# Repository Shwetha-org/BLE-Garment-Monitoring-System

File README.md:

# BLE Garment Monitoring System

## Overview

This project presents an end-to-end system for monitoring garment usage using a custom Bluetooth Low Energy (BLE) tag, edge processing, and a mobile application.

The system tracks garment states such as **worn**, **stored**, and **washed** by analyzing sensor data broadcast from a custom BLE-enabled garment tag.

---
## Custom BLE Garment Tag

<p align="center">
  Custom BLE garment tag with integrated motion (BMI270) and humidity (SHTC3) sensors, powered by a CR2032 coin cell.
</p>

---

## System Architecture

The system consists of four main components:

### 1. Hardware (`hardware/garment_tag/`)

* Custom PCB design (KiCad)
* BLE module (nRF52832 – Raytac MDBT42Q)
* Sensors:

  * BMI270 (motion / acceleration)
  * SHTC3 (humidity and temperature)
* Assembly and manufacturing files

---

### 2. Firmware (`firmware/garment_tag/`)

* Zephyr-based firmware for the BLE tag
* Reads sensor data and encodes it into BLE advertisement payloads
* Broadcasts data continuously

---

### 3. Edge Node (`edge/`)

* Runs on Raspberry Pi
* Scans BLE advertisements using Python and Bleak
* Processes data using filtering and aggregation
* Classifies garment states (worn / stored / washed)
* Stores data in SQLite database
* Exposes REST API (`/summary`) using Flask

---

### 4. Android Application (`android_app/garment_tracker_app/`)

* Built with Kotlin and Jetpack Compose
* Connects to edge node API
* Displays:

  * Current garment state
  * Wear count
  * Wash count
* Includes privacy controls and live updates

---

## Data Flow

1. Sensors on the BLE tag collect motion, humidity, and temperature
2. Firmware encodes data into BLE advertisements
3. Raspberry Pi scans and processes the data
4. Classification pipeline determines garment state
5. Results are stored locally and exposed via API
6. Android app fetches and displays usage summaries

---

## BLE Payload Structure

The edge node expects manufacturer-specific data in the following format:

* Byte 0 → motion (0 or 1)
* Byte 1 → humidity (%)
* Byte 2 → temperature offset (temp + 40)

Manufacturer ID: `1027`

---

## Getting Started

### 1. Hardware

* Assemble the custom BLE tag
* Flash firmware onto the nRF52832

### 2. Edge Node

```bash
cd edge
pip install -r requirements.txt
python pipeline_final.py
```

### 3. Android App

* Open `android_app/garment_tracker_app/` in Android Studio
* Update Raspberry Pi IP in the code
* Run the application

---

## Requirements

* Raspberry Pi with Bluetooth
* Custom BLE garment tag
* Android device
* Python 3.x

---

## Notes

* The system operates on a local network
* The Android app requires the Raspberry Pi API to be running
* BLE payload structure must match firmware and edge logic

---

## Documentation

Detailed documentation is available in:

* `docs/architecture.md` – system design and component overview  
* `docs/setup_guide.md` – installation and setup instructions  
* `docs/User_Manual.pdf` – how to use the system (end-user guide)

---

## Project Scope

This project focuses on:

* Edge-based processing (no cloud dependency)
* Privacy-preserving garment tracking
* Lightweight BLE-based sensing

---

## License

This project is developed for academic purposes.

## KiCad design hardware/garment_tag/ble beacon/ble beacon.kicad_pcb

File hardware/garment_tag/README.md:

# Garment Tag Hardware

## Overview

This folder contains the hardware design files for the custom BLE garment tag used in the garment monitoring system.

The garment tag is a custom-built embedded device that integrates a BLE module and sensors on a single PCB. It continuously broadcasts sensor data via BLE advertisements, which are received and processed by the Raspberry Pi edge node.

---

## Folder Structure

* `kicad/`
  Contains the KiCad schematic and PCB design files.

* `assembly/`
  Contains reference images of the assembled PCB.

* `manufacturing/`
  Contains Gerber files, drill files, and BOM used for PCB fabrication.

---

## Main Hardware Components

* Raytac MDBT42Q (nRF52832 BLE module used for BLE advertising)
* IMU sensor (used for motion and gyroscope data)
* Humidity sensor
* Coin cell battery (power supply)
* Custom PCB integrating all components into a wearable garment tag

The custom PCB integrates the BLE module and sensors into a single wearable device that continuously broadcasts environmental and motion data via BLE advertisements.

---

## KiCad Design Files

The PCB and schematic can be opened using KiCad:

```text
hardware/garment_tag/kicad/
```

Key files:

```text
ble beacon.kicad_pcb
ble beacon.kicad_sch
ble beacon.kicad_pro
```

---

## Manufacturing Files

Manufacturing files are located in:

```text
hardware/garment_tag/manufacturing/
```

These include:

* Copper layers
* Solder mask layers
* Silkscreen layers
* Drill files
* BOM (bill of materials) CSV

These files can be directly used for PCB fabrication.

---

## Assembly Reference

Assembly images are located in:

```text
hardware/garment_tag/assembly/
```

These show:

* Front of PCB
* Back of PCB
* Close-up component placement

They can be used as reference when assembling the board.

---

## Reproduction Steps

1. Open the KiCad project from `kicad/`.
2. Review the schematic and PCB layout.
3. Use the files in `manufacturing/` to fabricate the PCB.
4. Use the BOM to source components.
5. Assemble the PCB using the reference images in `assembly/`.
6. Flash firmware onto the BLE module using the nRF52 DK via SWD.
7. Power the board using a coin cell battery.
8. Verify that the device broadcasts BLE advertisement data.

---

## Notes

* The nRF52 DK is used only as a development and flashing tool.
* The custom garment tag PCB is the actual BLE device used in the system.
* The BLE advertisements from this device are processed by the edge node (`pipeline_final.py`).

---

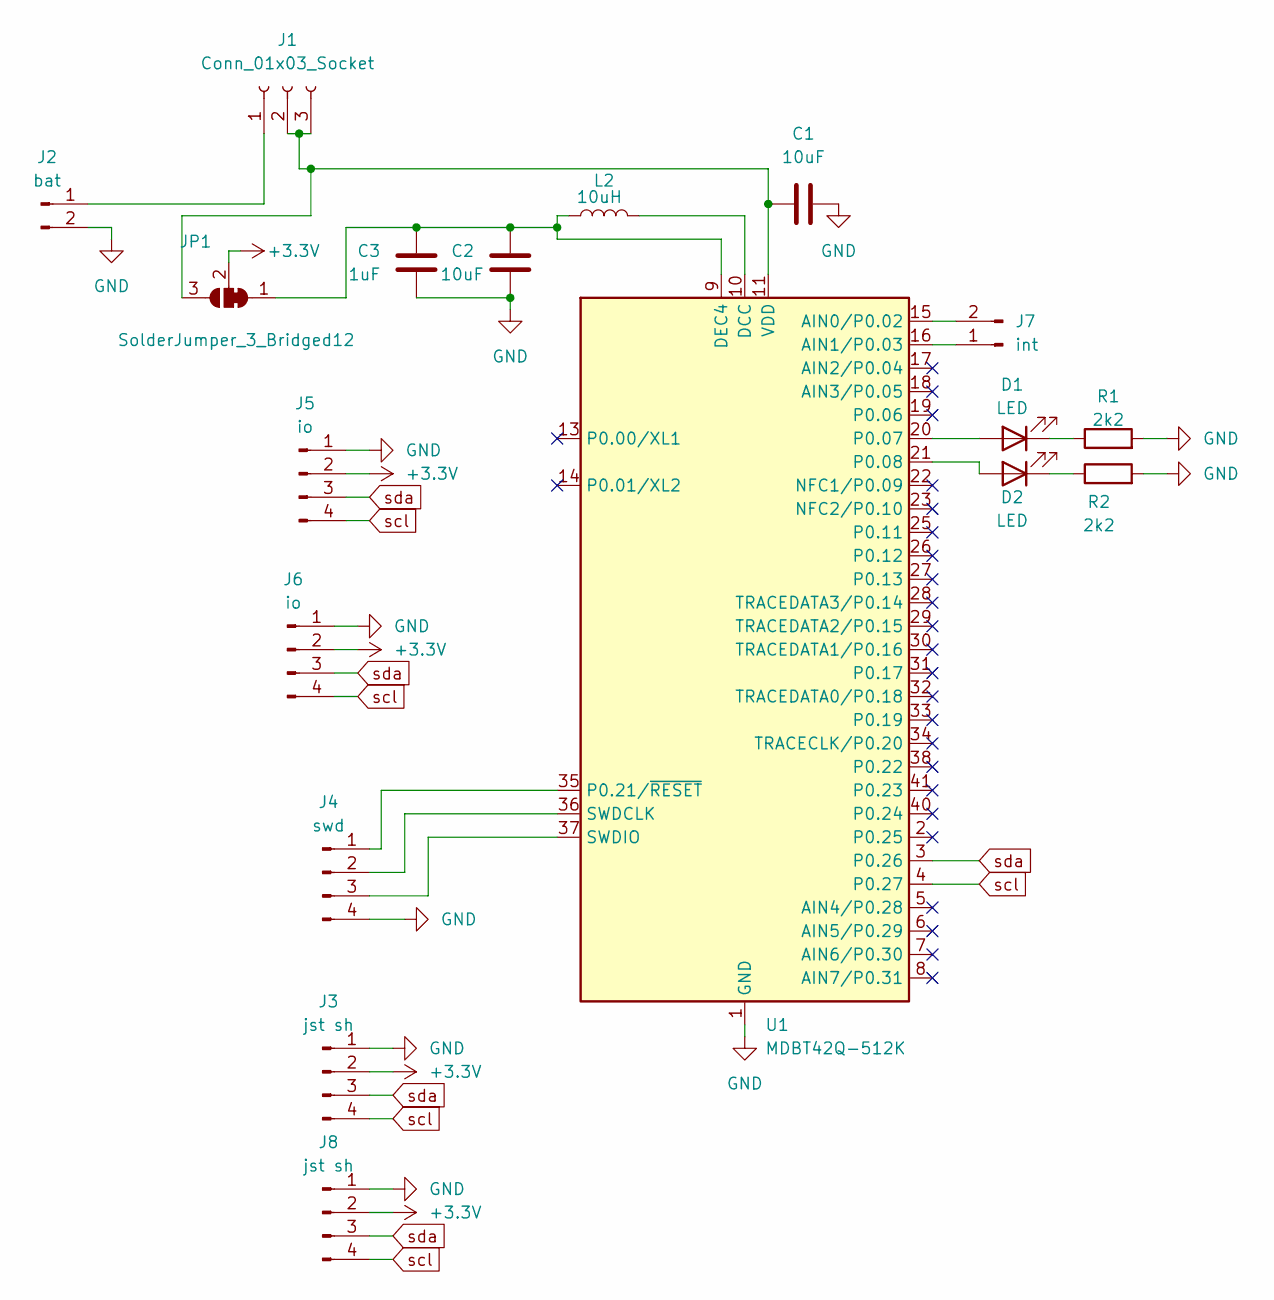
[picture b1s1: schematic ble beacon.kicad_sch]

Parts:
C1, C2: 10uF; C_0805_2012Metric
C3: 1uF; C_0805_2012Metric
D1, D2: LED; LED_0603_1608Metric
J1: Conn_01x03_Socket; PinHeader_1x03_P2.54mm_Vertical
J2: bat; BatteryHolder_Keystone_1060_1x2032
J3, J8: jst sh; JST_SH_SM04B-SRSS-TB_1x04-1MP_P1.00mm_Horizontal
J4: swd; PinHeader_1x04_P2.54mm_Vertical
J5, J6: io; PinHeader_1x04_P2.54mm_Vertical
J7: int; PinHeader_1x02_P2.54mm_Vertical
JP1: SolderJumper_3_Bridged12; SolderJumper-3_P1.3mm_Bridged12_RoundedPad1.0x1.5mm_NumberL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
L2: 10uH; L_Coilcraft_XAL6030-XXX
R1, R2: 2k2; R_0805_2012Metric
U1: MDBT42Q-512K; Raytac_MDBT42Q

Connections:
+3.3V: J3.2, J5.2, J6.2, J8.2, JP1.2 (C)
GND: C1.2, C2.1, C3.1, J2.2, J3.1, J3.MP, J4.4, J5.1, J6.1, J8.1, J8.MP, R1.2, R2.2, U1.1 (GND), U1.12 (GND), U1.24 (GND), U1.39 (GND)
unnamed: D1.2 (A), U1.20 (P0.07)
unnamed: D1.1 (K), R1.1
unnamed: D2.2 (A), U1.21 (P0.08)
unnamed: D2.1 (K), R2.1
unnamed: J1.1, J2.1
unnamed: C1.1, J1.2, J1.3, JP1.3 (B), U1.11 (VDD)
unnamed: J4.1, U1.35 (P0.21/~RESET)
unnamed: J4.2, U1.36 (SWDCLK)
unnamed: J4.3, U1.37 (SWDIO)
unnamed: J7.1, U1.16 (AIN1/P0.03)
unnamed: J7.2, U1.15 (AIN0/P0.02)
unnamed: C2.2, C3.2, JP1.1 (A), L2.1, U1.9 (DEC4)
unnamed: L2.2, U1.10 (DCC)
scl: J3.4, J5.4, J6.4, J8.4, U1.4 (P0.27)
sda: J3.3, J5.3, J6.3, J8.3, U1.3 (P0.26)

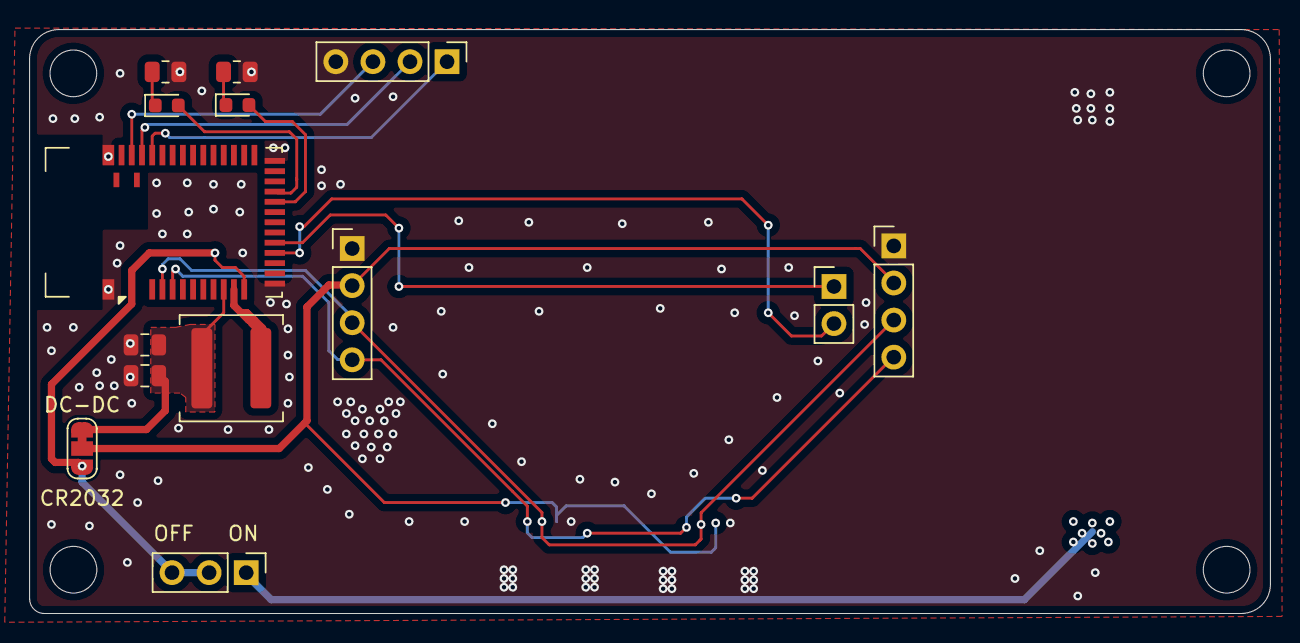
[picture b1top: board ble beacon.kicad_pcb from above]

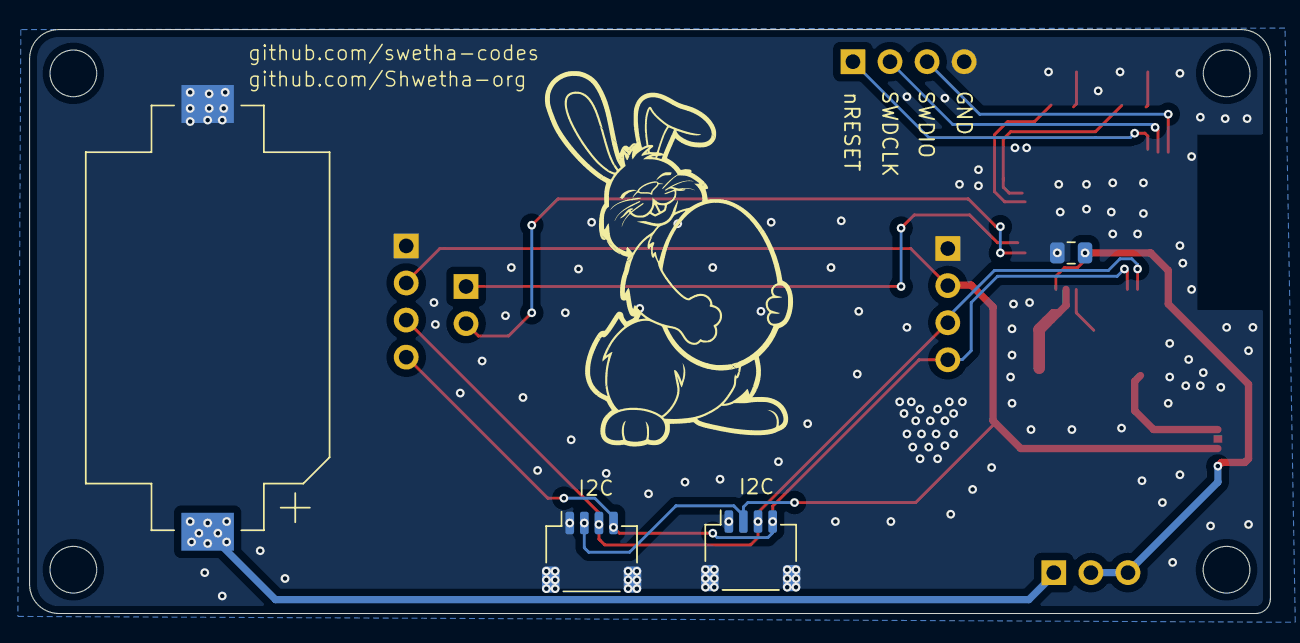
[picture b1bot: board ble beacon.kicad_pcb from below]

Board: 2 copper layers, 85.0 x 40.0 mm, 18 parts (4 on the bottom side), 17 nets.

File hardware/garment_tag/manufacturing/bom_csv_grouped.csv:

"Reference","Qty","Value","DNP","Exclude from BOM","Exclude from Board","Footprint","Datasheet"
"C1,C2","2","10uF","","","","Capacitor_SMD:C_0805_2012Metric",""
"C3","1","1uF","","","","Capacitor_SMD:C_0805_2012Metric",""
"D1,D2","2","LED","","","","LED_SMD:LED_0603_1608Metric",""
"J1","1","Conn_01x03_Socket","","","","Connector_PinHeader_2.54mm:PinHeader_1x03_P2.54mm_Vertical",""
"J2","1","bat","","","","Battery:BatteryHolder_Keystone_1060_1x2032",""
"J3,J8","2","jst sh","","","","Connector_JST:JST_SH_SM04B-SRSS-TB_1x04-1MP_P1.00mm_Horizontal",""
"J4","1","swd","","","","Connector_PinHeader_2.54mm:PinHeader_1x04_P2.54mm_Vertical",""
"J5,J6","2","io","","","","Connector_PinHeader_2.54mm:PinHeader_1x04_P2.54mm_Vertical",""
"J7","1","int","","","","Connector_PinHeader_2.54mm:PinHeader_1x02_P2.54mm_Vertical",""
"L2","1","10uH","","","","Inductor_SMD:L_Coilcraft_XAL6030-XXX",""
"R1,R2","2","2k2","","","","Resistor_SMD:R_0805_2012Metric",""
"U1","1","MDBT42Q-512K","","","","RF_Module:Raytac_MDBT42Q","https://www.raytac.com/download/index.php?index_id=27"

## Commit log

2026-04-05 Initial project structure and README
2026-04-05 Organize BLE tag PCB: move manufacturing outputs to outputs/
2026-04-05 Describe BLE Garment Monitoring System and repo structure
2026-04-21 Add BLE beacon assembly photos and notes for tag PCB
2026-04-21 Replace beacon assembly HEIC photos with JPGs
2026-04-21 Update beacon assembly JPG photos
2026-05-04 Organize garment tag hardware files
2026-05-04 Add documentation structure
2026-05-04 Add edge node software structure
2026-05-04 Add edge Python dependencies
2026-05-04 Add garment tag hardware documentation
2026-05-04 Add firmware folder structure and placeholder
2026-05-04 Remove firmware folder for now
2026-05-04 Add system architecture documentation
2026-05-04 Add setup guide
2026-05-04 Add API documentation
2026-05-04 Add Android application
2026-05-04 Add Android app files instead of embedded repository
2026-05-04 Add Android app README
2026-05-05 Add BLE tag firmware and documentation
2026-05-05 Rename folders for cleaner structure
2026-05-05 Add BLE tag image
2026-05-05 Add user manual pdf
2026-05-05 Rename docs/BLE_Garment_Tag_User_Manual_final.pdf to User_Manual.pdf
2026-05-05 Update README documentation links
